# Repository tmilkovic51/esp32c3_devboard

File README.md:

# ESP32-C3 Development board
A development board integrating the socket for easily swapping the ESP32-C3-WROOM-02 module.
It also includes:
* USB type C connector connected to USB hub (Microchip USB2514Bi) with these downstream ports:
  1. USB - UART adapter (Silabs CP2102N) connected to ESP32-C3 RXD and TXD pins - can be used for serial programming
  2. ESP32-C3 USB Serial/JTAG peripheral - can be used for serial programming and/or debugging the ESP32-C3
* ESD protection diodes on USB connector (SRV05-4)
* 4x SK6805 individually addressable LEDs connected to ESP32-C3's GPIO8 pin
* Pin headers compatible with ESP32-C3-DevkitC development kit by Espressif
* Solder bridges for disconnecting the USB - UART and USB hub from ESP32-C3's pins

## PCB front:

## PCB back:

## KiCAD version
This project is compatible with KiCAD version v6.

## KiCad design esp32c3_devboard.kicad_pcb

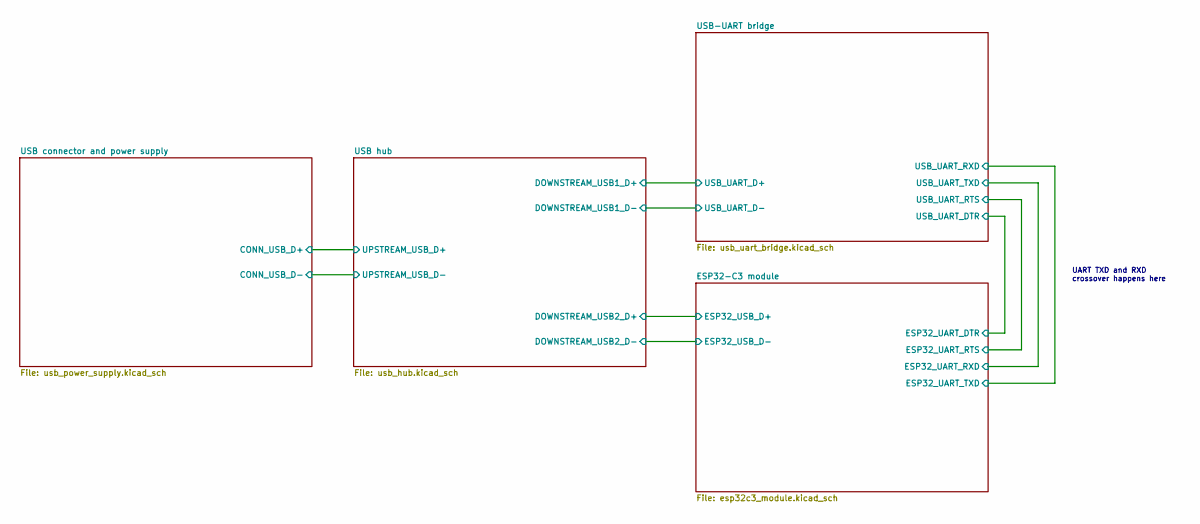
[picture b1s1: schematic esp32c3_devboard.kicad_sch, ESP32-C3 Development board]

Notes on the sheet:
UART TXD and RXD crossover happens here

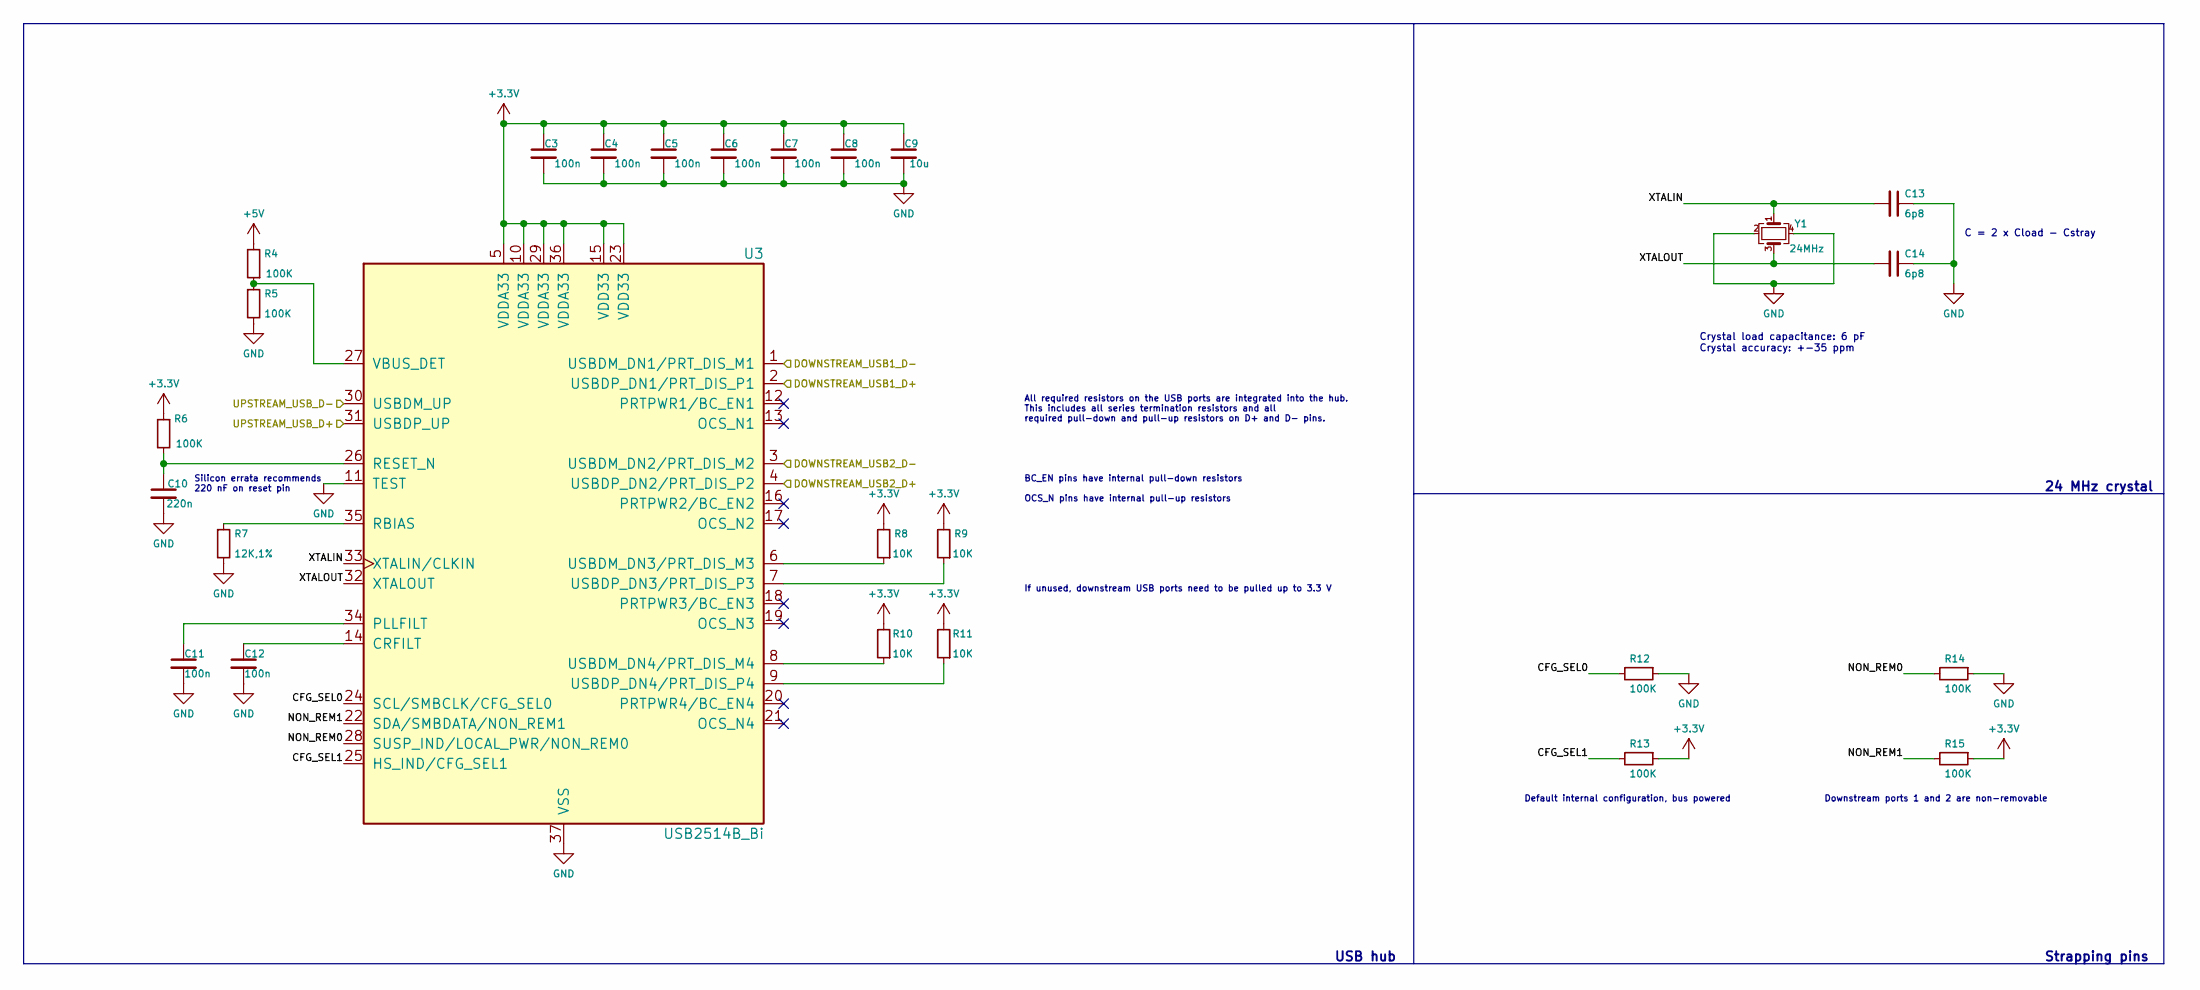
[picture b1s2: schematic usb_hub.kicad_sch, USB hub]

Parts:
C3, C4, C5, C6, C7, C8, C11, C12: 100n; C_0402_1005Metric; LCSC C307331
C9: 10u; C_0603_1608Metric; LCSC C19702
C10: 220n; C_0402_1005Metric; LCSC C16772
C13, C14: 6p8; C_0402_1005Metric; LCSC C1576
R4, R5, R6, R12, R13, R14, R15: 100K; R_0402_1005Metric; LCSC C25741
R7: 12K,1%; R_0402_1005Metric; LCSC C25752
R8, R9, R10, R11: 10K; R_0402_1005Metric; LCSC C25744
U3: USB2514B_Bi; QFN-36-1EP_6x6mm_P0.5mm_EP3.7x3.7mm; LCSC C220679
Y1: 24MHz; Crystal_SMD_2016-4Pin_2.0x1.6mm; LCSC C194420

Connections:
+3.3V: C3.1, C4.1, C5.1, C6.1, C7.1, C8.1, C9.1, R6.1, R8.2, R9.2, R10.2, R11.2, R13.1, R15.1, U3.5 (VDDA33), U3.10 (VDDA33), U3.15 (VDD33), U3.23 (VDD33), U3.29 (VDDA33), U3.36 (VDDA33); also elsewhere on the board
+5V: R4.2; also elsewhere on the board
/ESP32-C3 module/ESP32_USB_D+: U3.4 (USBDP_DN2/PRT_DIS_P2); also elsewhere on the board
/ESP32-C3 module/ESP32_USB_D-: U3.3 (USBDM_DN2/PRT_DIS_M2); also elsewhere on the board
/USB connector and power supply/CONN_USB_D+: U3.31 (USBDP_UP); also elsewhere on the board
/USB connector and power supply/CONN_USB_D-: U3.30 (USBDM_UP); also elsewhere on the board
/USB hub/CFG_SEL0: R12.2, U3.24 (SCL/SMBCLK/CFG_SEL0)
/USB hub/CFG_SEL1: R13.2, U3.25 (HS_IND/CFG_SEL1)
/USB hub/DOWNSTREAM_USB1_D+: U3.2 (USBDP_DN1/PRT_DIS_P1); also elsewhere on the board
/USB hub/DOWNSTREAM_USB1_D-: U3.1 (USBDM_DN1/PRT_DIS_M1); also elsewhere on the board
/USB hub/NON_REM0: R14.2, U3.28 (SUSP_IND/LOCAL_PWR/NON_REM0)
/USB hub/NON_REM1: R15.2, U3.22 (SDA/SMBDATA/NON_REM1)
/USB hub/XTALIN: C13.2, U3.33 (XTALIN/CLKIN), Y1.1
/USB hub/XTALOUT: C14.2, U3.32 (XTALOUT), Y1.3
GND: C3.2, C4.2, C5.2, C6.2, C7.2, C8.2, C9.2, C10.2, C11.2, C12.2, C13.1, C14.1, R5.2, R7.2, R12.1, R14.1, U3.11 (TEST), U3.37 (VSS), Y1.2, Y1.4; also elsewhere on the board
unnamed: C10.1, R6.2, U3.26 (RESET_N)
unnamed: C11.1, U3.34 (PLLFILT)
unnamed: C12.1, U3.14 (CRFILT)
unnamed: R4.1, R5.1, U3.27 (VBUS_DET)
unnamed: R7.1, U3.35 (RBIAS)
unnamed: R8.1, U3.6 (USBDM_DN3/PRT_DIS_M3)
unnamed: R9.1, U3.7 (USBDP_DN3/PRT_DIS_P3)
unnamed: R10.1, U3.8 (USBDM_DN4/PRT_DIS_M4)
unnamed: R11.1, U3.9 (USBDP_DN4/PRT_DIS_P4)

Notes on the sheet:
Strapping pins
C = 2 x Cload - Cstray
USB hub
24 MHz crystal
BC_EN pins have internal pull-down resistors
Downstream ports 1 and 2 are non-removable
Silicon errata recommends 220 nF on reset pin
All required resistors on the USB ports are integrated into the hub. This includes all series termination resistors and all required pull-down and pull-up resistors on D+ and D- pins.
If unused, downstream USB ports need to be pulled up to 3.3 V
Default internal configuration, bus powered
OCS_N pins have internal pull-up resistors
Crystal load capacitance: 6 pF Crystal accuracy: +-35 ppm

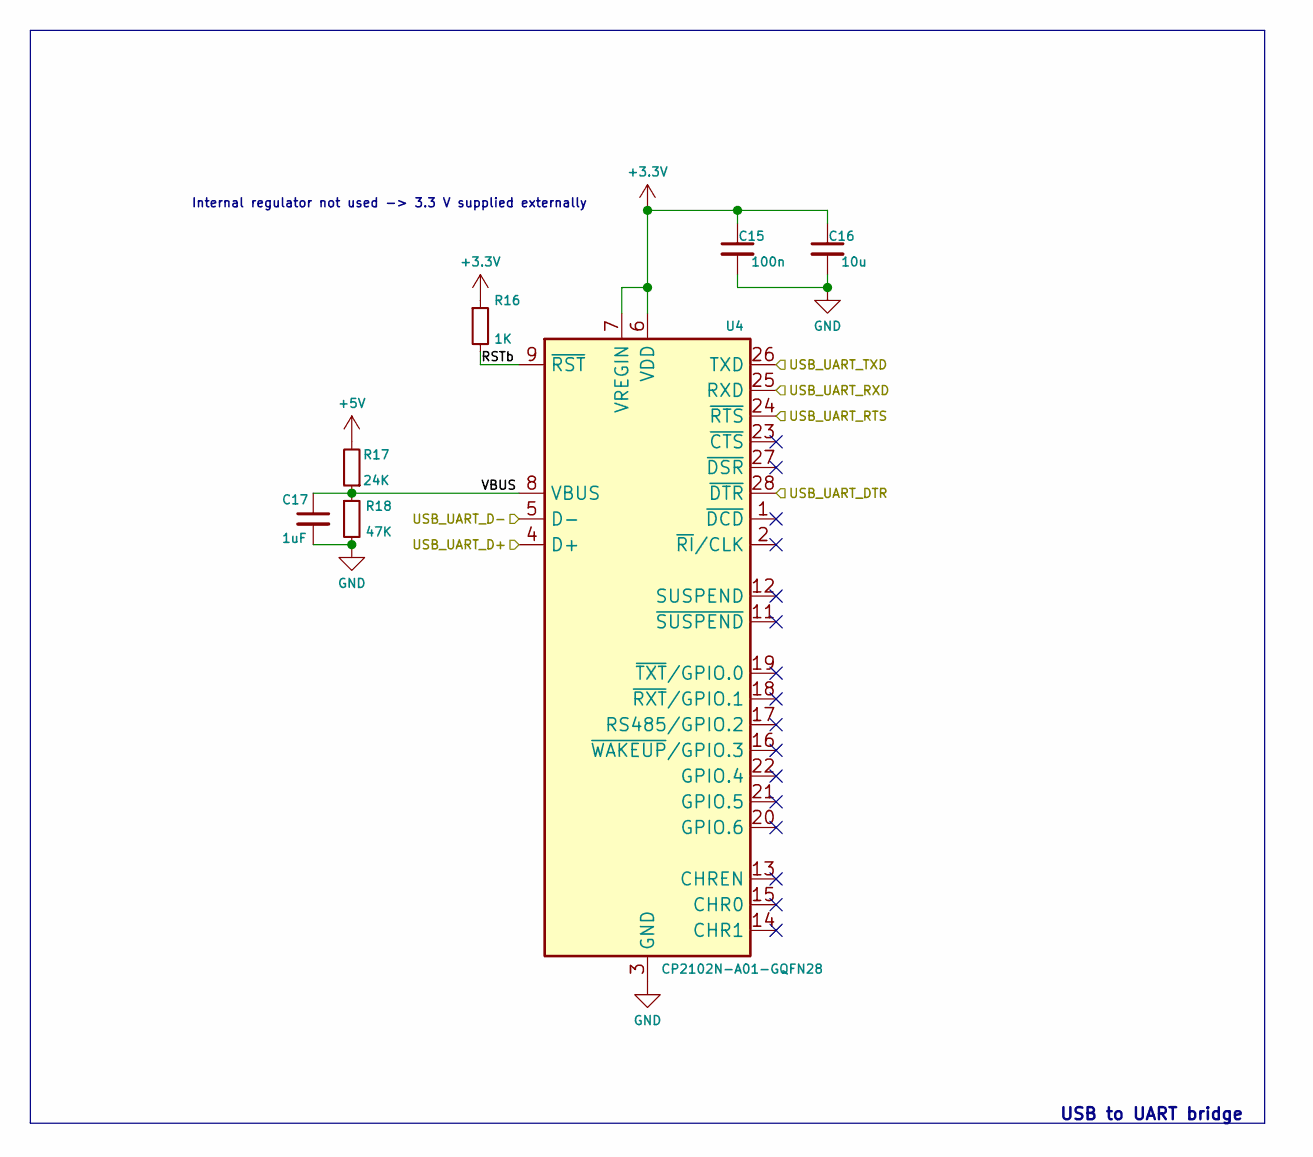
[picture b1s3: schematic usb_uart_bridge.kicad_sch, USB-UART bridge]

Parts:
C15: 100n; C_0402_1005Metric; LCSC C307331
C16: 10u; C_0603_1608Metric; LCSC C19702
C17: 1uF; C_0402_1005Metric; LCSC C52923
R16: 1K; R_0402_1005Metric; LCSC C11702
R17: 24K; R_0402_1005Metric; LCSC C25769
R18: 47K; R_0402_1005Metric; LCSC C25792
U4: CP2102N-A01-GQFN28; QFN-28-1EP_5x5mm_P0.5mm_EP3.35x3.35mm; LCSC C6568

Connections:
+3.3V: C15.1, C16.1, R16.1, U4.6 (VDD), U4.7 (VREGIN); also elsewhere on the board
+5V: R17.2; also elsewhere on the board
/ESP32-C3 module/ESP32_UART_DTR: U4.28 (~DTR); also elsewhere on the board
/ESP32-C3 module/ESP32_UART_RTS: U4.24 (~RTS); also elsewhere on the board
/ESP32-C3 module/ESP32_UART_RXD: U4.26 (TXD); also elsewhere on the board
/ESP32-C3 module/ESP32_UART_TXD: U4.25 (RXD); also elsewhere on the board
/USB hub/DOWNSTREAM_USB1_D+: U4.4 (D+); also elsewhere on the board
/USB hub/DOWNSTREAM_USB1_D-: U4.5 (D-); also elsewhere on the board
/USB-UART bridge/RSTb: R16.2, U4.9 (~RST)
/USB-UART bridge/VBUS: C17.1, R17.1, R18.1, U4.8 (VBUS)
GND: C15.2, C16.2, C17.2, R18.2, U4.3 (GND), U4.29 (GND); also elsewhere on the board

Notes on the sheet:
USB to UART bridge
Internal regulator not used -> 3.3 V supplied externally

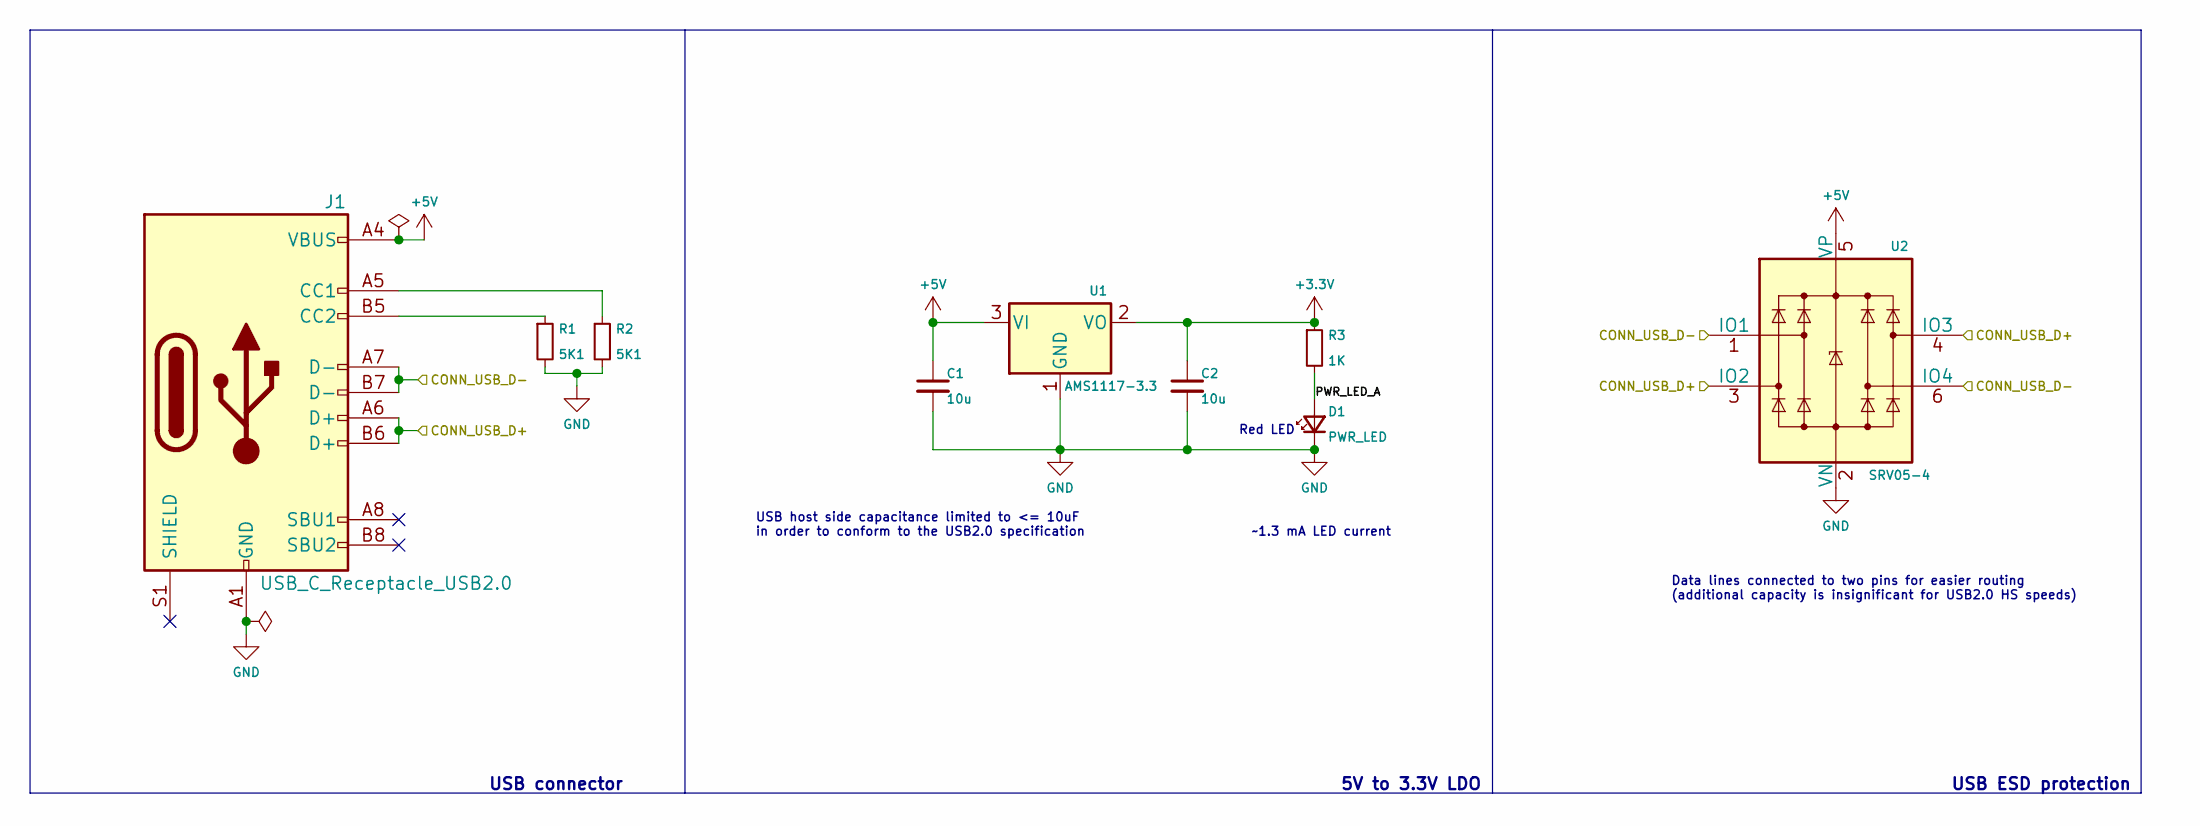
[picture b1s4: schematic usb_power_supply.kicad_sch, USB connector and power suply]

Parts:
C1, C2: 10u; C_0603_1608Metric; LCSC C19702
D1: PWR_LED; LED_0603_1608Metric; LCSC C2286
J1: USB_C_Receptacle_USB2.0; USB_C_Receptacle_XKB_U262-16XN-4BVC11; LCSC C393939
R1, R2: 5K1; R_0402_1005Metric; LCSC C25905
R3: 1K; R_0402_1005Metric; LCSC C11702
U1: AMS1117-3.3; SOT-223-3_TabPin2; LCSC C6186
U2: SRV05-4; SOT-23-6; LCSC C85364

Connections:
+3.3V: C2.1, R3.1, U1.2 (VO); also elsewhere on the board
+5V: C1.1, J1.A4 (VBUS), J1.A9 (VBUS), J1.B4 (VBUS), J1.B9 (VBUS), U1.3 (VI), U2.5 (VP); also elsewhere on the board
/USB connector and power supply/CONN_USB_D+: J1.A6 (D+), J1.B6 (D+), U2.3 (IO2), U2.4 (IO3); also elsewhere on the board
/USB connector and power supply/CONN_USB_D-: J1.A7 (D-), J1.B7 (D-), U2.1 (IO1), U2.6 (IO4); also elsewhere on the board
/USB connector and power supply/PWR_LED_A: D1.2 (A), R3.2
GND: C1.2, C2.2, D1.1 (K), J1.A1 (GND), J1.A12 (GND), J1.B1 (GND), J1.B12 (GND), R1.2, R2.2, U1.1 (GND), U2.2 (VN); also elsewhere on the board
unnamed: J1.A5 (CC1), R2.1
unnamed: J1.B5 (CC2), R1.1

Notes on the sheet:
USB ESD protection
USB connector
USB host side capacitance limited to <= 10uF in order to conform to the USB2.0 specification
5V to 3.3V LDO
~1.3 mA LED current
Red LED
Data lines connected to two pins for easier routing (additional capacity is insignificant for USB2.0 HS speeds)

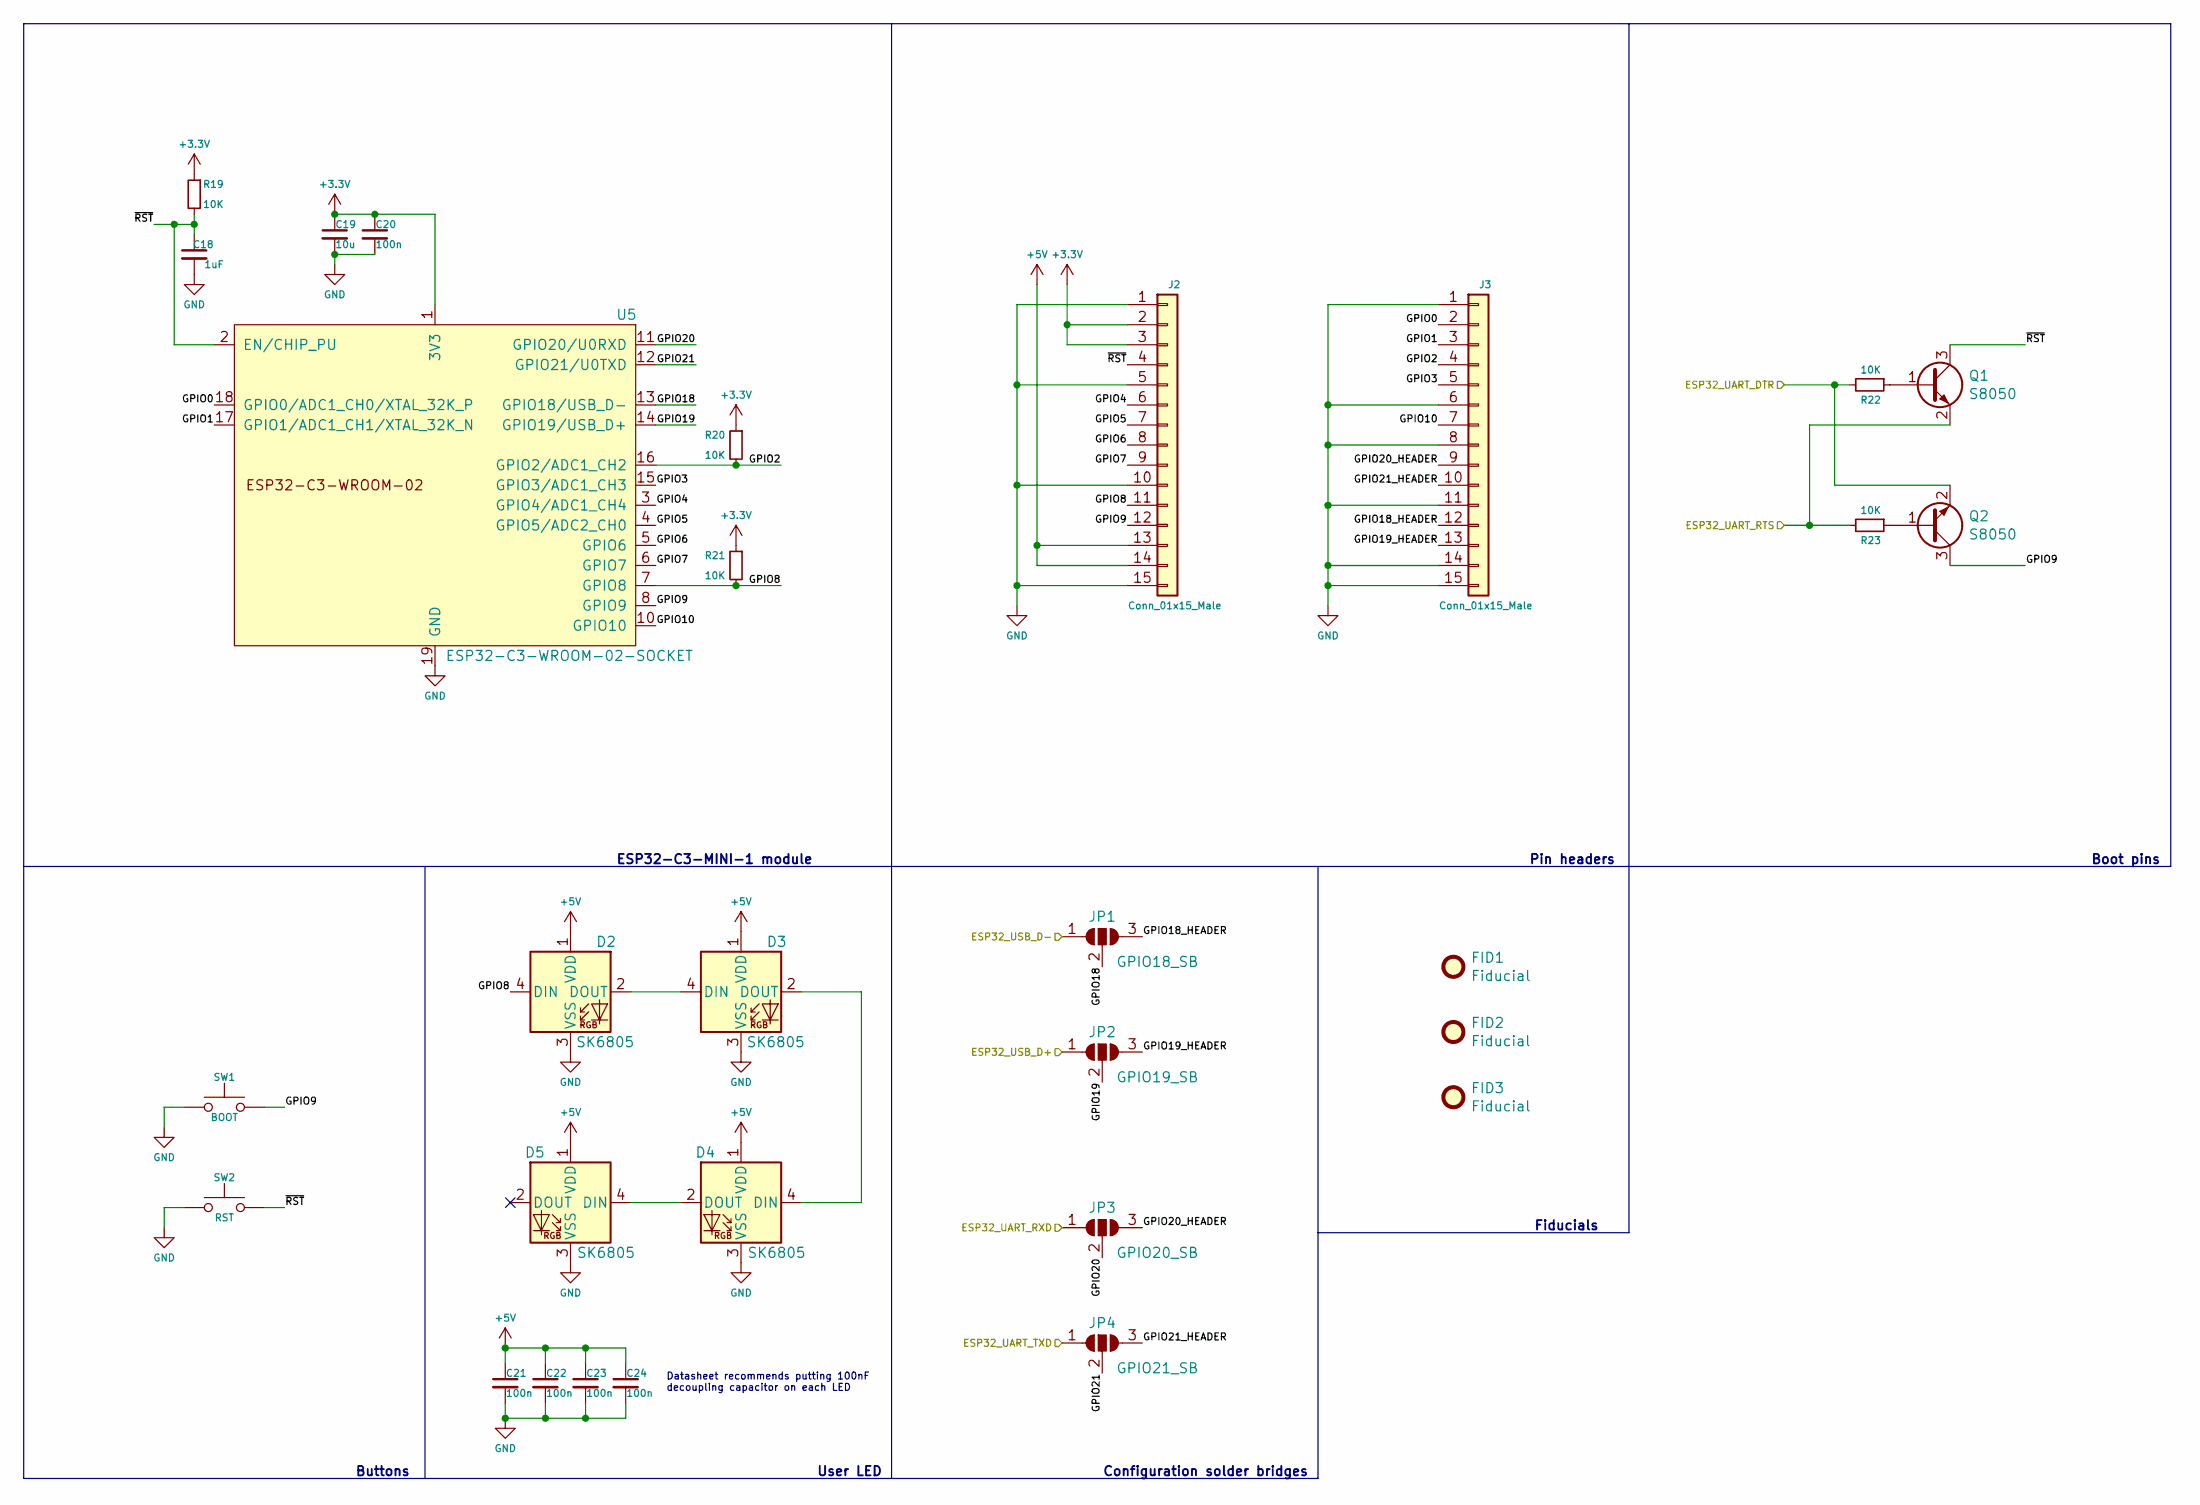
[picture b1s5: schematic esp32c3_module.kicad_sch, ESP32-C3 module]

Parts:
C18: 1uF; C_0402_1005Metric; LCSC C52923
C19: 10u; C_0603_1608Metric; LCSC C19702
C20, C21, C22, C23, C24: 100n; C_0402_1005Metric; LCSC C307331
D2, D3, D4, D5: SK6805; LED_SK6805_E14_1.4x1.4mm_P0.4mm; LCSC C2909055
FID1, FID2, FID3: Fiducial; Fiducial_0.5mm_Mask1mm
J2, J3: Conn_01x15_Male; PinHeader_1x15_P2.54mm_Vertical
JP1: GPIO18_SB; SolderJumper-3_P1.3mm_Open_RoundedPad1.0x1.5mm
JP2: GPIO19_SB; SolderJumper-3_P1.3mm_Open_RoundedPad1.0x1.5mm
JP3: GPIO20_SB; SolderJumper-3_P1.3mm_Open_RoundedPad1.0x1.5mm
JP4: GPIO21_SB; SolderJumper-3_P1.3mm_Open_RoundedPad1.0x1.5mm
Q1, Q2: S8050; SOT-23; LCSC C2146
R19, R20, R21, R22, R23: 10K; R_0402_1005Metric; LCSC C25744
SW1: BOOT; SW_SPST_CK_RS282G05A3
SW2: RST; SW_SPST_CK_RS282G05A3
U5: ESP32-C3-WROOM-02-SOCKET

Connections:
+3.3V: C19.1, C20.1, J2.2, J2.3, R19.1, R20.1, R21.1, U5.1 (3V3); also elsewhere on the board
+5V: C21.1, C22.1, C23.1, C24.1, D2.1 (VDD), D3.1 (VDD), D4.1 (VDD), D5.1 (VDD), J2.13, J2.14; also elsewhere on the board
/ESP32-C3 module/ESP32_UART_DTR: Q2.2 (E), R22.2; also elsewhere on the board
/ESP32-C3 module/ESP32_UART_RTS: Q1.2 (E), R23.2; also elsewhere on the board
/ESP32-C3 module/ESP32_UART_RXD: JP3.1 (A); also elsewhere on the board
/ESP32-C3 module/ESP32_UART_TXD: JP4.1 (A); also elsewhere on the board
/ESP32-C3 module/ESP32_USB_D+: JP2.1 (A); also elsewhere on the board
/ESP32-C3 module/ESP32_USB_D-: JP1.1 (A); also elsewhere on the board
/ESP32-C3 module/GPIO0: J3.2, U5.18 (GPIO0/ADC1_CH0/XTAL_32K_P)
/ESP32-C3 module/GPIO1: J3.3, U5.17 (GPIO1/ADC1_CH1/XTAL_32K_N)
/ESP32-C3 module/GPIO2: J3.4, R20.2, U5.16 (GPIO2/ADC1_CH2)
/ESP32-C3 module/GPIO3: J3.5, U5.15 (GPIO3/ADC1_CH3)
/ESP32-C3 module/GPIO4: J2.6, U5.3 (GPIO4/ADC1_CH4)
/ESP32-C3 module/GPIO5: J2.7, U5.4 (GPIO5/ADC2_CH0)
/ESP32-C3 module/GPIO6: J2.8, U5.5 (GPIO6)
/ESP32-C3 module/GPIO7: J2.9, U5.6 (GPIO7)
/ESP32-C3 module/GPIO8: D2.4 (DIN), J2.11, R21.2, U5.7 (GPIO8)
/ESP32-C3 module/GPIO9: J2.12, Q2.3 (C), SW1.2, U5.8 (GPIO9)
/ESP32-C3 module/GPIO10: J3.7, U5.10 (GPIO10)
/ESP32-C3 module/GPIO18: JP1.2 (C), U5.13 (GPIO18/USB_D-)
/ESP32-C3 module/GPIO18_HEADER: J3.12, JP1.3 (B)
/ESP32-C3 module/GPIO19: JP2.2 (C), U5.14 (GPIO19/USB_D+)
/ESP32-C3 module/GPIO19_HEADER: J3.13, JP2.3 (B)
/ESP32-C3 module/GPIO20: JP3.2 (C), U5.11 (GPIO20/U0RXD)
/ESP32-C3 module/GPIO20_HEADER: J3.9, JP3.3 (B)
/ESP32-C3 module/GPIO21: JP4.2 (C), U5.12 (GPIO21/U0TXD)
/ESP32-C3 module/GPIO21_HEADER: J3.10, JP4.3 (B)
/ESP32-C3 module/~RST: C18.1, J2.4, Q1.3 (C), R19.2, SW2.2, U5.2 (EN/CHIP_PU)
GND: C18.2, C19.2, C20.2, C21.2, C22.2, C23.2, C24.2, D2.3 (VSS), D3.3 (VSS), D4.3 (VSS), D5.3 (VSS), J2.1, J2.5, J2.10, J2.15, J3.1, J3.6, J3.8, J3.11, J3.14, J3.15, SW1.1, SW2.1, U5.9 (GND), U5.19 (GND); also elsewhere on the board
unnamed: D2.2 (DOUT), D3.4 (DIN)
unnamed: D3.2 (DOUT), D4.4 (DIN)
unnamed: D4.2 (DOUT), D5.4 (DIN)
unnamed: Q1.1 (B), R22.1
unnamed: Q2.1 (B), R23.1

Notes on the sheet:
Configuration solder bridges
Fiducials
Boot pins
Pin headers
ESP32-C3-MINI-1 module
Datasheet recommends putting 100nF decoupling capacitor on each LED
Buttons
User LED

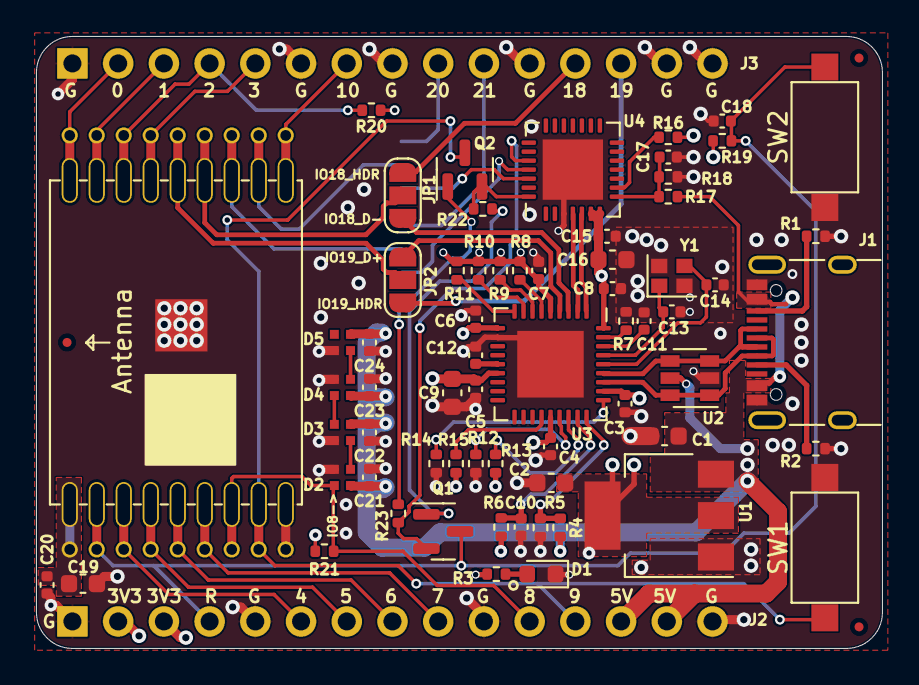
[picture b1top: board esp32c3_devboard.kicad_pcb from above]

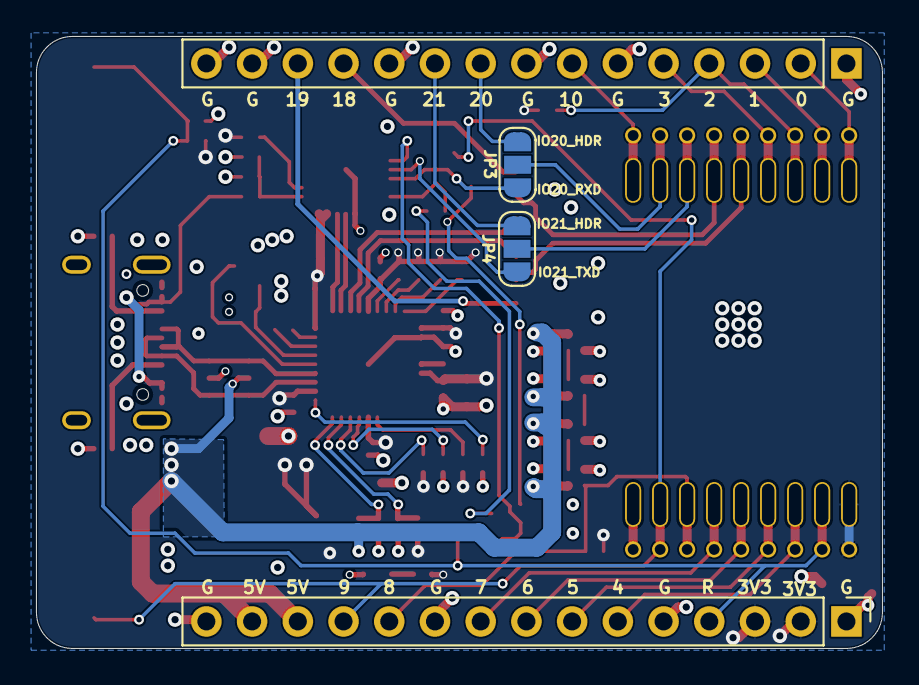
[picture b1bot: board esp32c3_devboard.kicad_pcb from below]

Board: 4 copper layers, 47.0 x 34.0 mm, 72 parts (4 on the bottom side), 58 nets.

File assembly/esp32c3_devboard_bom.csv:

Comment,Designator,Footprint,LCSC
"220n","C10","Capacitor_SMD:C_0402_1005Metric","C16772"
"6p8","C13,C14","Capacitor_SMD:C_0402_1005Metric","C1576"
"1uF","C17,C18","Capacitor_SMD:C_0402_1005Metric","C52923"
"100n","C3,C4,C5,C6,C7,C8,C11,C12,C15,C20,C21,C22,C23,C24","Capacitor_SMD:C_0402_1005Metric","C307331"
"10u","C1,C2,C9,C16,C19","Capacitor_SMD:C_0603_1608Metric","C19702"
"PWR_LED","D1","LED_SMD:LED_0603_1608Metric","C2286"
"SK6805","D2,D3,D4,D5","LED_custom:LED_SK6805_E14_1.4x1.4mm_P0.4mm","C2909055"
"USB_C_Receptacle_USB2.0","J1","Connector_USB:USB_C_Receptacle_XKB_U262-16XN-4BVC11","C393939"
"S8050","Q1,Q2","Package_TO_SOT_SMD:SOT-23","C2146"
"10K","R8,R9,R10,R11,R19,R20,R21,R22,R23","Resistor_SMD:R_0402_1005Metric","C25744"
"100K","R4,R5,R6,R12,R13,R14,R15","Resistor_SMD:R_0402_1005Metric","C25741"
"24K","R17","Resistor_SMD:R_0402_1005Metric","C25769"
"47K","R18","Resistor_SMD:R_0402_1005Metric","C25792"
"5K1","R1,R2","Resistor_SMD:R_0402_1005Metric","C25905"
"1K","R3,R16","Resistor_SMD:R_0402_1005Metric","C11702"
"12K,1%","R7","Resistor_SMD:R_0402_1005Metric","C25752"
"AMS1117-3.3","U1","Package_TO_SOT_SMD:SOT-223-3_TabPin2","C6186"
"SRV05-4","U2","Package_TO_SOT_SMD:SOT-23-6","C85364"
"USB2514B_Bi","U3","Package_DFN_QFN:QFN-36-1EP_6x6mm_P0.5mm_EP3.7x3.7mm","C220679"
"CP2102N-A01-GQFN28","U4","Package_DFN_QFN:QFN-28-1EP_5x5mm_P0.5mm_EP3.35x3.35mm","C6568"
"24MHz","Y1","Crystal:Crystal_SMD_2016-4Pin_2.0x1.6mm","C194420"

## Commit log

2022-09-17 Initialize KiCad project
    Add Espressif KiCad library as submodule
2022-09-17 Update schematic with ESP32 module, power supply and USB to serial
2022-09-26 Place components on PCB
2022-09-26 Add pullup on GPIO2 strapping pin
2022-10-01 Add micro USB step files
2022-11-19 Change button silkscreen labels to RST and BOOT
2022-11-19 Add Microchip USB2514Bi USB hub to schematic and PCB
2022-11-19 Configure bootstrapping pins on USB hub IC
2022-11-20 Update schematic to be hierarchical
2023-02-01 Replace CP2102 with CH340X
    Also add BJTs to ESP32C3 strapping pins
2025-02-15 Use ESP32-C3-WROOM-02 module
2025-02-16 Change USB UART adapter to CP2102
2025-02-16 Add LCSC part numbers for all components
2025-02-18 Replace WS2812B with SK6805 RGB LED
2025-02-18 PCB: Rough component placement done
2025-02-18 PCB: Routing done
2025-02-20 Add fiducials, finish routing
2025-02-21 Specify QR code location, prepare for fabrication and assembly at JLCPCB
2025-02-21 Update README with PCB images
2025-02-21 Add files for PCB fabrication and assembly compatible with JLCPCB
2025-04-08 add 3D model for esp32 with coil pins
2025-07-31 Update project to KiCAD v6, fix BJT wrong symbol pinout

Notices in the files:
esp32c3_devboard.kicad_pcb:
Copyright: Tomislav Milkovic
